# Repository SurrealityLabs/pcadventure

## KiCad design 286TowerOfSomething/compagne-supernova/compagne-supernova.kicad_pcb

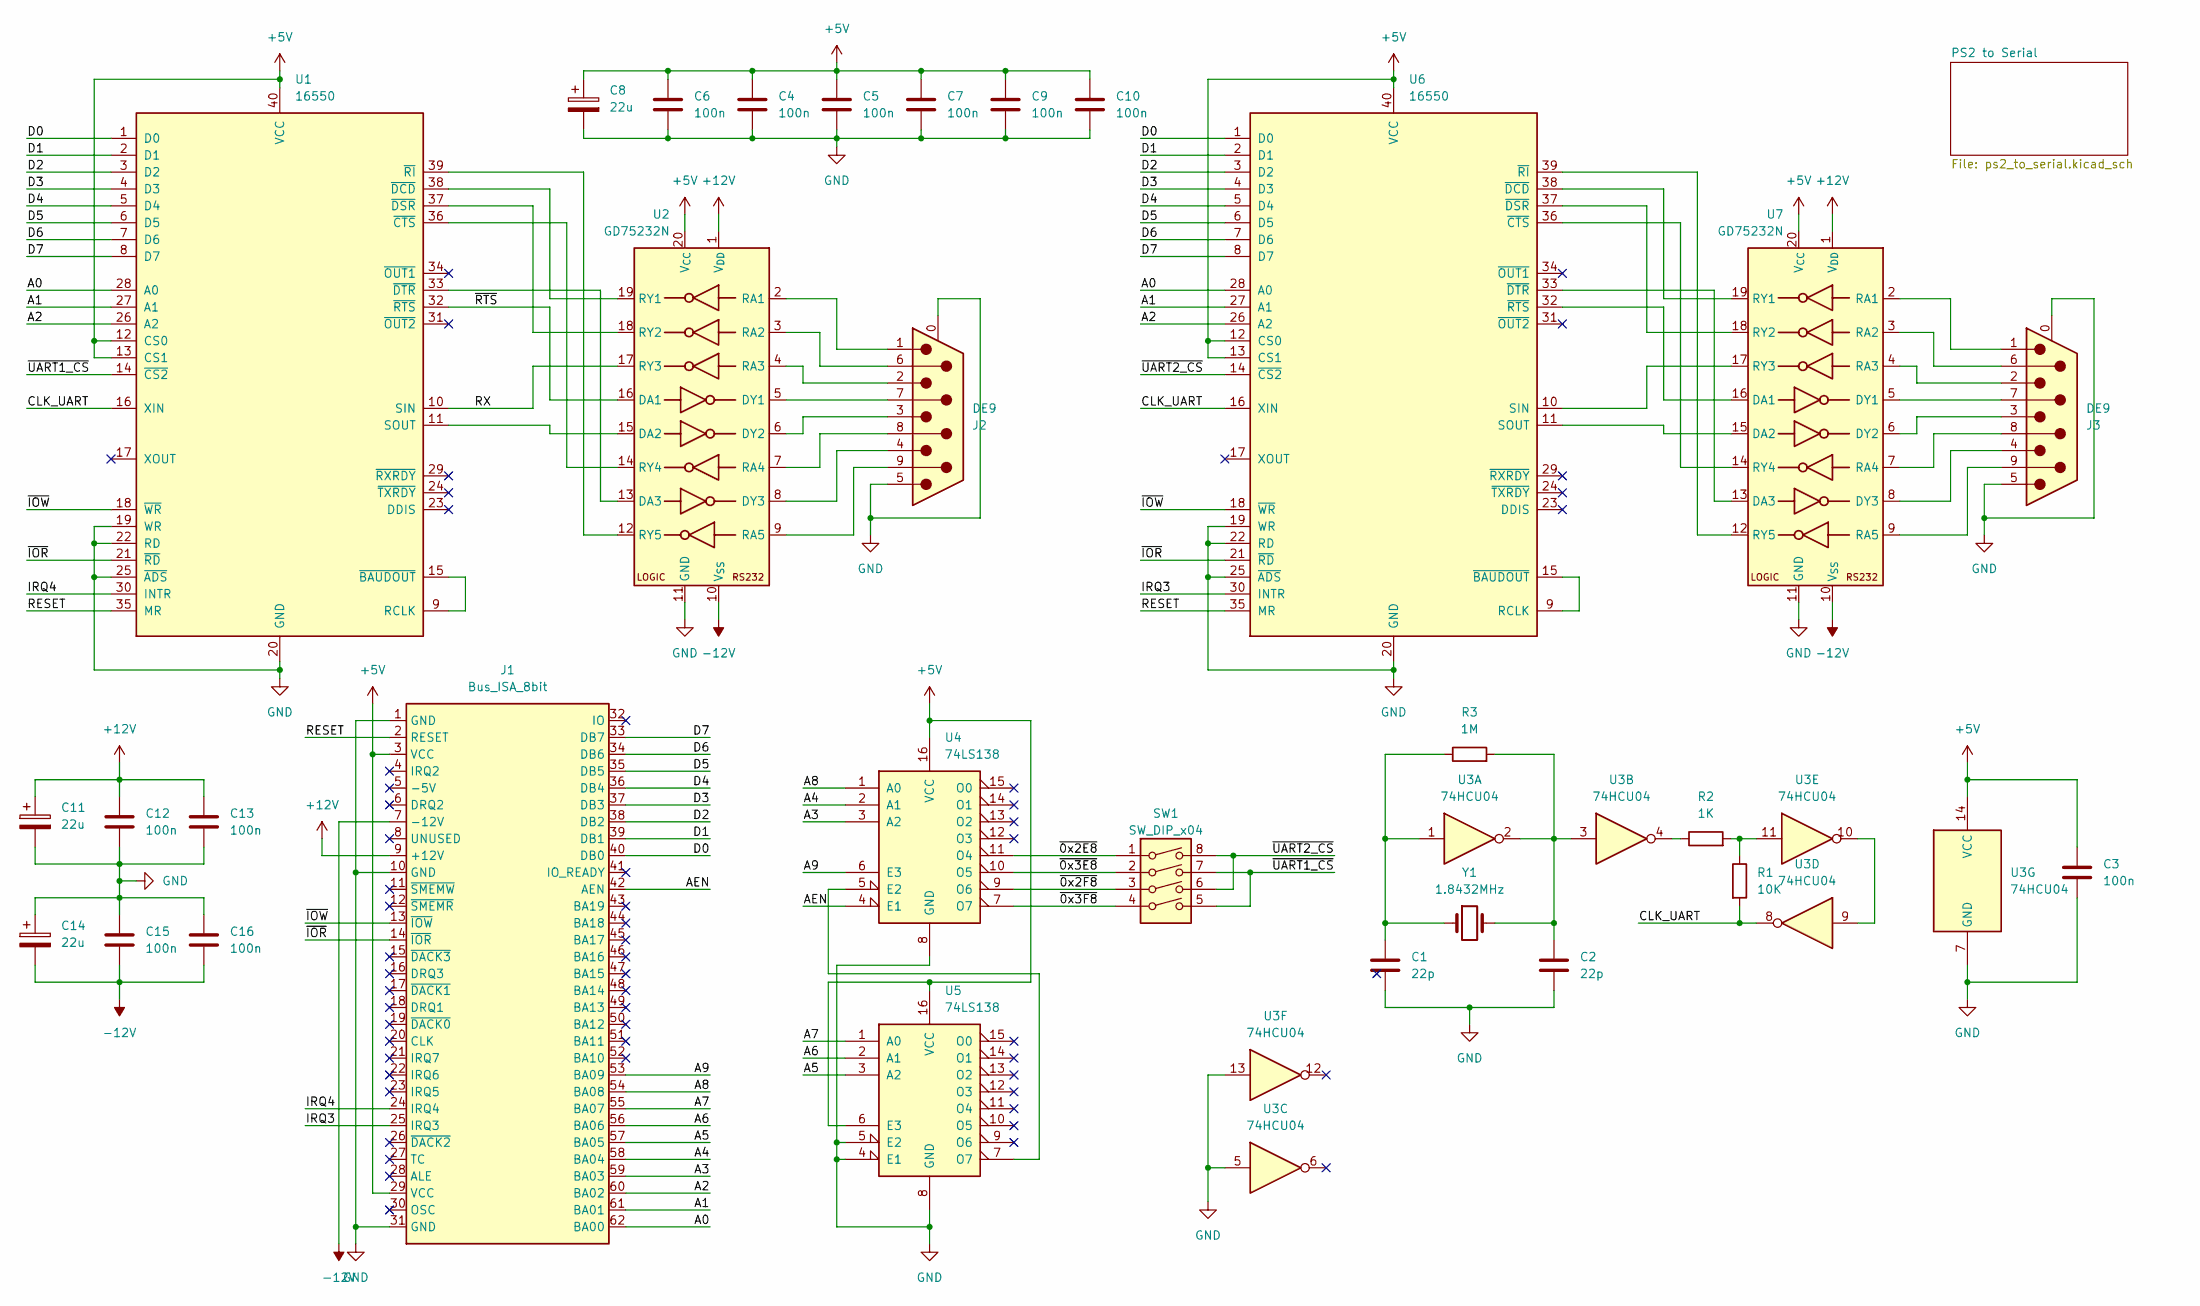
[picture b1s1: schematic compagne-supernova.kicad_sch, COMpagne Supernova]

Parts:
C1, C2: 22p; C_0603_1608Metric_Pad1.08x0.95mm_HandSolder
C3, C4, C5, C6, C7, C9, C10, C12, C13, C15, C16: 100n; C_0603_1608Metric_Pad1.08x0.95mm_HandSolder
C8, C11, C14: 22u; CP_Elec_5x5.3
J1: Bus_ISA_8bit; BUS_AT_8BIT
J2, J3: DE9; DSUB-9_Male_Horizontal_P2.77x2.84mm_EdgePinOffset7.70mm_Hou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
R1: 10K; R_0603_1608Metric_Pad0.98x0.95mm_HandSolder
R2: 1K; R_0603_1608Metric_Pad0.98x0.95mm_HandSolder
R3: 1M; R_0603_1608Metric_Pad0.98x0.95mm_HandSolder
SW1: SW_DIP_x04; SW_DIP_SPSTx04_Slide_9.78x12.34mm_W7.62mm_P2.54mm
U1, U6: 16550; DIP-40_W15.24mm
U2, U7: GD75232N; DIP-20_W7.62mm
U3: 74HCU04; SO-14_3.9x8.65mm_P1.27mm
U4, U5: 74LS138; DIP-16_W7.62mm
Y1: 1.8432MHz; Crystal_HC49-U_Vertical

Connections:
+5V: C3.1, C4.1, C5.1, C6.1, C7.1, C8.1, C9.1, C10.1, J1.3 (VCC), J1.29 (VCC), U1.12 (CS0), U1.13 (CS1), U1.40 (VCC), U2.20 (V_{CC}), U3.14 (VCC), U4.16 (VCC), U5.6 (E3), U5.16 (VCC), U6.12 (CS0), U6.13 (CS1), U6.40 (VCC), U7.20 (V_{CC}); also elsewhere on the board
+12V: C11.1, C12.1, C13.1, J1.9 (+12V), U2.1 (V_{DD}), U7.1 (V_{DD})
-12V: C14.2, C15.2, C16.2, J1.7 (-12V), U2.10 (V_{SS}), U7.10 (V_{SS})
/A0: J1.62 (BA00), U1.28 (A0), U6.28 (A0)
/A1: J1.61 (BA01), U1.27 (A1), U6.27 (A1)
/A2: J1.60 (BA02), U1.26 (A2), U6.26 (A2)
/A3: J1.59 (BA03), U4.3 (A2)
/A4: J1.58 (BA04), U4.2 (A1)
/A5: J1.57 (BA05), U5.3 (A2)
/A6: J1.56 (BA06), U5.2 (A1)
/A7: J1.55 (BA07), U5.1 (A0)
/A8: J1.54 (BA08), U4.1 (A0)
/A9: J1.53 (BA09), U4.6 (E3)
/AEN: J1.42 (AEN), U4.4 (E1)
/CLK_UART: R1.2, U1.16 (XIN), U3.8, U6.16 (XIN)
/D0: J1.40 (DB0), U1.1 (D0), U6.1 (D0)
/D1: J1.39 (DB1), U1.2 (D1), U6.2 (D1)
/D2: J1.38 (DB2), U1.3 (D2), U6.3 (D2)
/D3: J1.37 (DB3), U1.4 (D3), U6.4 (D3)
/D4: J1.36 (DB4), U1.5 (D4), U6.5 (D4)
/D5: J1.35 (DB5), U1.6 (D5), U6.6 (D5)
/D6: J1.34 (DB6), U1.7 (D6), U6.7 (D6)
/D7: J1.33 (DB7), U1.8 (D7), U6.8 (D7)
/IRQ3: J1.25 (IRQ3), U6.30 (INTR)
/IRQ4: J1.24 (IRQ4), U1.30 (INTR)
/RESET: J1.2 (RESET), U1.35 (MR), U6.35 (MR)
/RX: U1.10 (SIN), U2.17 (RY3)
/~0x2E8: SW1.1, U4.11 (O4)
/~0x2F8: SW1.3, U4.9 (O6)
/~0x3E8: SW1.2, U4.10 (O5)
/~0x3F8: SW1.4, U4.7 (O7)
/~IOR: J1.14 (~IOR), U1.21 (~RD), U6.21 (~RD)
/~IOW: J1.13 (~IOW), U1.18 (~WR), U6.18 (~WR)
/~RTS: U1.32 (~RTS), U2.16 (DA1)
/~UART1_CS: SW1.5, SW1.7, U1.14 (~CS2)
/~UART2_CS: SW1.6, SW1.8, U6.14 (~CS2)
GND: C1.2, C2.2, C3.2, C4.2, C5.2, C6.2, C7.2, C8.2, C9.2, C10.2, C11.2, C12.2, C13.2, C14.1, C15.1, C16.1, J1.1 (GND), J1.10 (GND), J1.31 (GND), J2.0 (PAD), J2.5, J3.0 (PAD), J3.5, U1.19 (WR), U1.20 (GND), U1.22 (RD), U1.25 (~ADS), U2.11 (GND), U3.5, U3.7 (GND), U3.13, U4.8 (GND), U5.4 (E1), U5.5 (E2), U5.8 (GND), U6.19 (WR), U6.20 (GND), U6.22 (RD), U6.25 (~ADS), U7.11 (GND); also elsewhere on the board
unnamed: C1.1, R3.1, U3.1, Y1.1
unnamed: C2.1, R3.2, U3.2, U3.3, Y1.2
unnamed: R1.1, R2.2, U3.11
unnamed: R2.1, U3.4
unnamed: U1.9 (RCLK), U1.15 (~BAUDOUT)
unnamed: U1.11 (SOUT), U2.15 (DA2)
unnamed: U1.36 (~CTS), U2.14 (RY4)
unnamed: U1.38 (~DCD), U2.19 (RY1)
unnamed: U1.37 (~DSR), U2.18 (RY2)
unnamed: U1.33 (~DTR), U2.13 (DA3)
unnamed: U1.39 (~RI), U2.12 (RY5)
unnamed: J2.7, U2.5 (DY1)
unnamed: J2.3, U2.6 (DY2)
unnamed: J2.4, U2.8 (DY3)
unnamed: J2.1, U2.2 (RA1)
unnamed: J2.6, U2.3 (RA2)
unnamed: J2.2, U2.4 (RA3)
unnamed: J2.8, U2.7 (RA4)
unnamed: J2.9, U2.9 (RA5)
unnamed: U3.9, U3.10
unnamed: U4.5 (E2), U5.7 (O7)
unnamed: U6.9 (RCLK), U6.15 (~BAUDOUT)
unnamed: U6.10 (SIN), U7.17 (RY3)
unnamed: U6.11 (SOUT), U7.15 (DA2)
unnamed: U6.36 (~CTS), U7.14 (RY4)
unnamed: U6.38 (~DCD), U7.19 (RY1)
unnamed: U6.37 (~DSR), U7.18 (RY2)
unnamed: U6.33 (~DTR), U7.13 (DA3)
unnamed: U6.39 (~RI), U7.12 (RY5)
unnamed: U6.32 (~RTS), U7.16 (DA1)
unnamed: J3.7, U7.5 (DY1)
unnamed: J3.3, U7.6 (DY2)
unnamed: J3.4, U7.8 (DY3)
unnamed: J3.1, U7.2 (RA1)
unnamed: J3.6, U7.3 (RA2)
unnamed: J3.2, U7.4 (RA3)
unnamed: J3.8, U7.7 (RA4)
unnamed: J3.9, U7.9 (RA5)

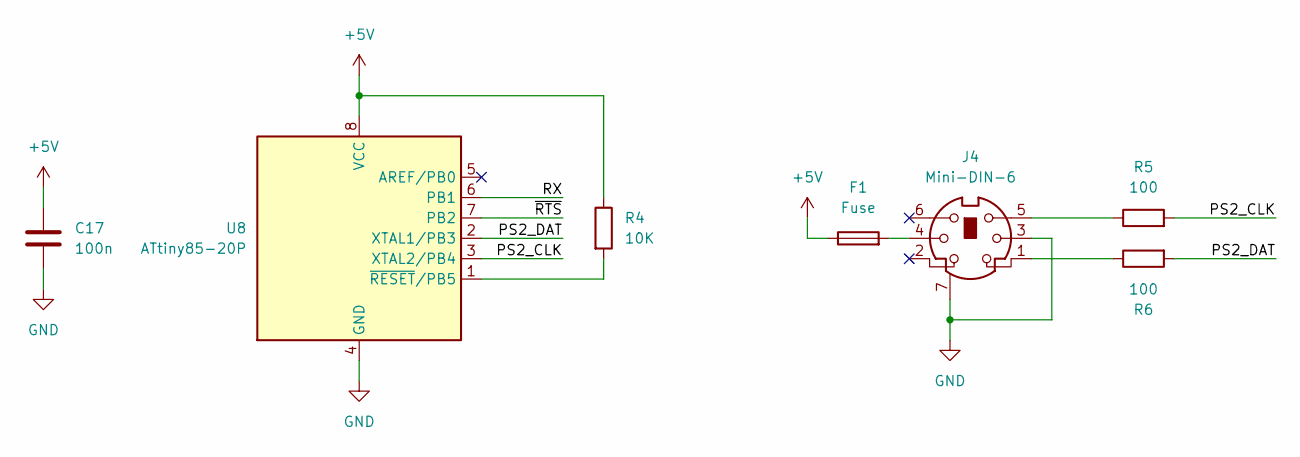
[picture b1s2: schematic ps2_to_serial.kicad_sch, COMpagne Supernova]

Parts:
C17: 100n; C_0603_1608Metric_Pad1.08x0.95mm_HandSolder
F1: Fuse; Fuse_1206_3216Metric_Pad1.42x1.75mm_HandSolder
J4: Mini-DIN-6; CUI_MD-60SGK
R4: 10K; R_0603_1608Metric_Pad0.98x0.95mm_HandSolder
R5, R6: 100; R_0603_1608Metric_Pad0.98x0.95mm_HandSolder
U8: ATtiny85-20P; DIP-8_W7.62mm

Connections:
+5V: C17.1, F1.1, R4.1, U8.8 (VCC); also elsewhere on the board
/PS2 to Serial/PS2_CLK: R5.2, U8.3 (XTAL2/PB4)
/PS2 to Serial/PS2_DAT: R6.2, U8.2 (XTAL1/PB3)
/PS2 to Serial/RX: U8.6 (PB1)
/PS2 to Serial/~RTS: U8.7 (PB2)
GND: C17.2, J4.3, J4.7, U8.4 (GND); also elsewhere on the board
unnamed: F1.2, J4.4
unnamed: J4.1, R6.1
unnamed: J4.5, R5.1
unnamed: R4.2, U8.1 (~RESET/PB5)

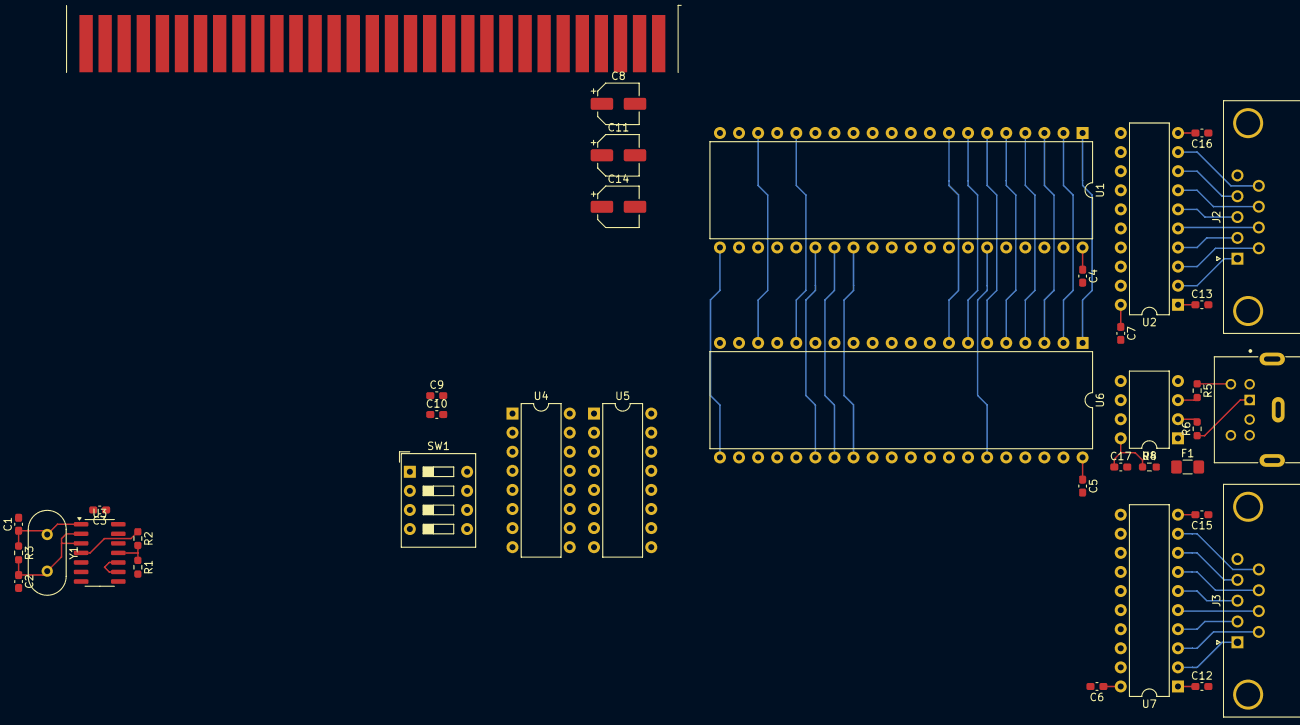
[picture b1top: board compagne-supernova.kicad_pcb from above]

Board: 2 copper layers, 38 parts (0 on the bottom side), 81 nets.

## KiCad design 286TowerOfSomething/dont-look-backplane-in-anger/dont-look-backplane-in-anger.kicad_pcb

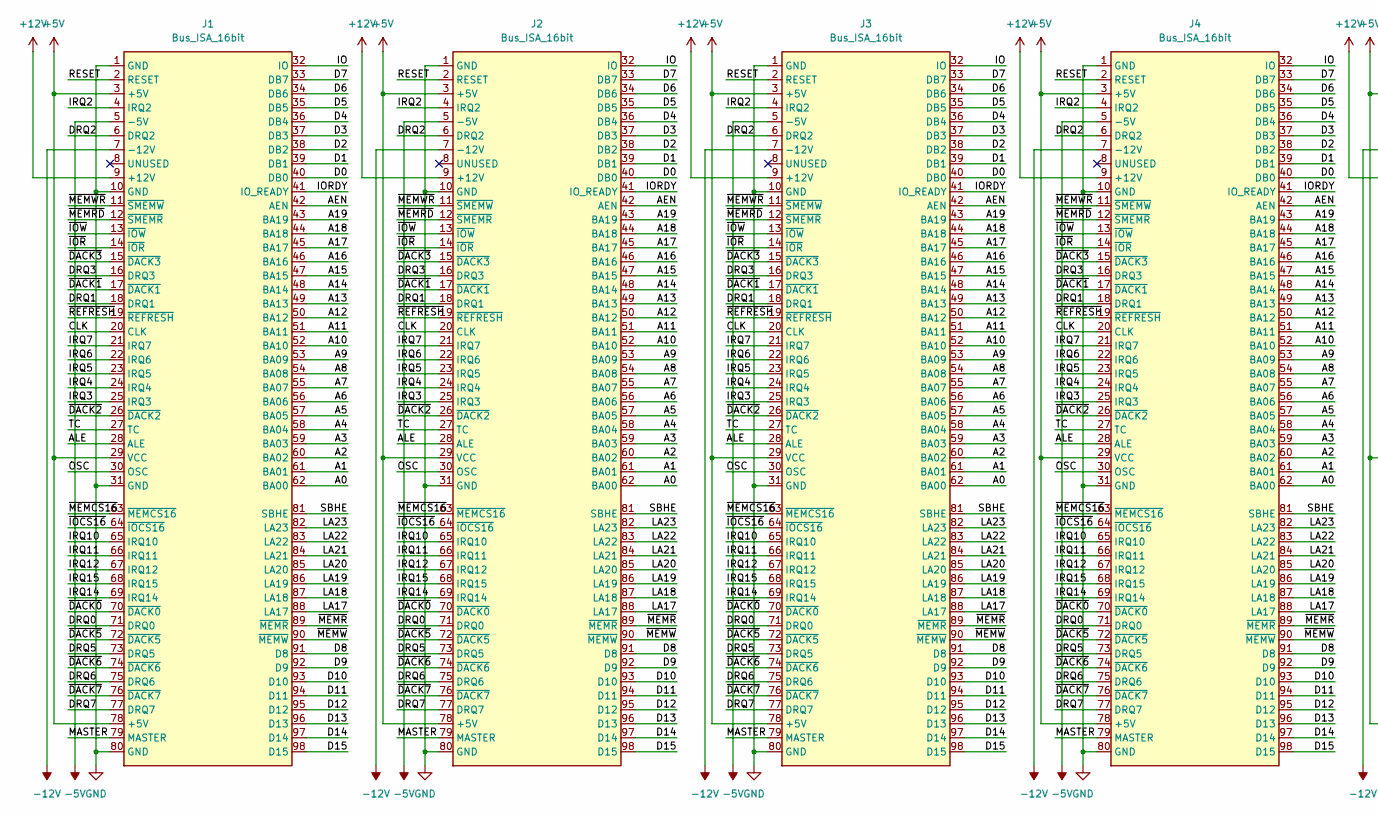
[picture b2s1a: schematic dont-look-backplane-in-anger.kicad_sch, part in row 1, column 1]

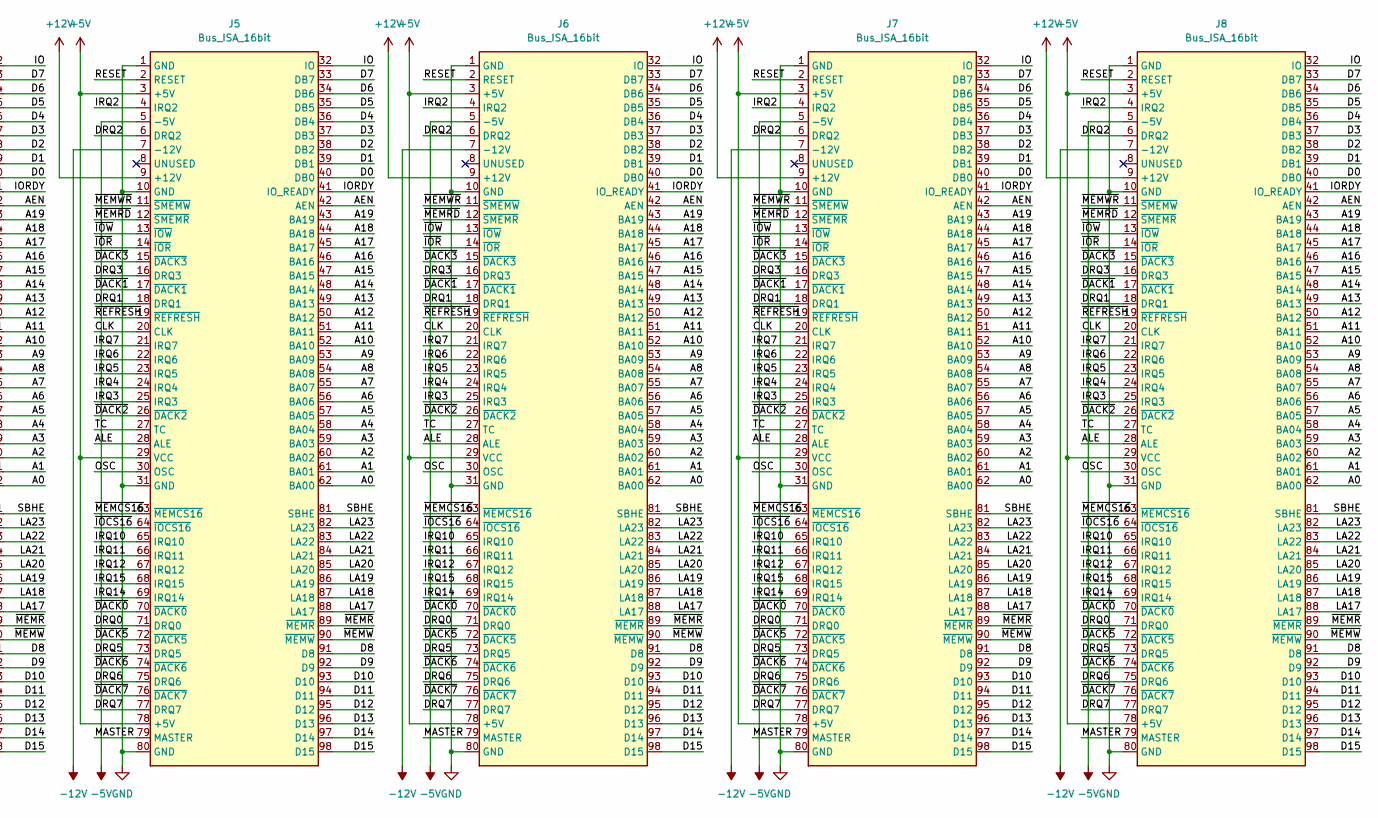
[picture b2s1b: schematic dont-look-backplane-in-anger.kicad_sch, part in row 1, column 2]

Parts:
J1, J2, J3, J4, J5, J6, J7, J8: Bus_ISA_16bit; 645169-3

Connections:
+5V: J1.3 (+5V), J1.29 (VCC), J1.78 (+5V), J2.3 (+5V), J2.29 (VCC), J2.78 (+5V), J3.3 (+5V), J3.29 (VCC), J3.78 (+5V), J4.3 (+5V), J4.29 (VCC), J4.78 (+5V), J5.3 (+5V), J5.29 (VCC), J5.78 (+5V), J6.3 (+5V), J6.29 (VCC), J6.78 (+5V), J7.3 (+5V), J7.29 (VCC), J7.78 (+5V), J8.3 (+5V), J8.29 (VCC), J8.78 (+5V)
+12V: J1.9 (+12V), J2.9 (+12V), J3.9 (+12V), J4.9 (+12V), J5.9 (+12V), J6.9 (+12V), J7.9 (+12V), J8.9 (+12V)
-5V: J1.5 (-5V), J2.5 (-5V), J3.5 (-5V), J4.5 (-5V), J5.5 (-5V), J6.5 (-5V), J7.5 (-5V), J8.5 (-5V)
-12V: J1.7 (-12V), J2.7 (-12V), J3.7 (-12V), J4.7 (-12V), J5.7 (-12V), J6.7 (-12V), J7.7 (-12V), J8.7 (-12V)
/A0: J1.62 (BA00), J2.62 (BA00), J3.62 (BA00), J4.62 (BA00), J5.62 (BA00), J6.62 (BA00), J7.62 (BA00), J8.62 (BA00)
/A1: J1.61 (BA01), J2.61 (BA01), J3.61 (BA01), J4.61 (BA01), J5.61 (BA01), J6.61 (BA01), J7.61 (BA01), J8.61 (BA01)
/A2: J1.60 (BA02), J2.60 (BA02), J3.60 (BA02), J4.60 (BA02), J5.60 (BA02), J6.60 (BA02), J7.60 (BA02), J8.60 (BA02)
/A3: J1.59 (BA03), J2.59 (BA03), J3.59 (BA03), J4.59 (BA03), J5.59 (BA03), J6.59 (BA03), J7.59 (BA03), J8.59 (BA03)
/A4: J1.58 (BA04), J2.58 (BA04), J3.58 (BA04), J4.58 (BA04), J5.58 (BA04), J6.58 (BA04), J7.58 (BA04), J8.58 (BA04)
/A5: J1.57 (BA05), J2.57 (BA05), J3.57 (BA05), J4.57 (BA05), J5.57 (BA05), J6.57 (BA05), J7.57 (BA05), J8.57 (BA05)
/A6: J1.56 (BA06), J2.56 (BA06), J3.56 (BA06), J4.56 (BA06), J5.56 (BA06), J6.56 (BA06), J7.56 (BA06), J8.56 (BA06)
/A7: J1.55 (BA07), J2.55 (BA07), J3.55 (BA07), J4.55 (BA07), J5.55 (BA07), J6.55 (BA07), J7.55 (BA07), J8.55 (BA07)
/A8: J1.54 (BA08), J2.54 (BA08), J3.54 (BA08), J4.54 (BA08), J5.54 (BA08), J6.54 (BA08), J7.54 (BA08), J8.54 (BA08)
/A9: J1.53 (BA09), J2.53 (BA09), J3.53 (BA09), J4.53 (BA09), J5.53 (BA09), J6.53 (BA09), J7.53 (BA09), J8.53 (BA09)
/A10: J1.52 (BA10), J2.52 (BA10), J3.52 (BA10), J4.52 (BA10), J5.52 (BA10), J6.52 (BA10), J7.52 (BA10), J8.52 (BA10)
/A11: J1.51 (BA11), J2.51 (BA11), J3.51 (BA11), J4.51 (BA11), J5.51 (BA11), J6.51 (BA11), J7.51 (BA11), J8.51 (BA11)
/A12: J1.50 (BA12), J2.50 (BA12), J3.50 (BA12), J4.50 (BA12), J5.50 (BA12), J6.50 (BA12), J7.50 (BA12), J8.50 (BA12)
/A13: J1.49 (BA13), J2.49 (BA13), J3.49 (BA13), J4.49 (BA13), J5.49 (BA13), J6.49 (BA13), J7.49 (BA13), J8.49 (BA13)
/A14: J1.48 (BA14), J2.48 (BA14), J3.48 (BA14), J4.48 (BA14), J5.48 (BA14), J6.48 (BA14), J7.48 (BA14), J8.48 (BA14)
/A15: J1.47 (BA15), J2.47 (BA15), J3.47 (BA15), J4.47 (BA15), J5.47 (BA15), J6.47 (BA15), J7.47 (BA15), J8.47 (BA15)
/A16: J1.46 (BA16), J2.46 (BA16), J3.46 (BA16), J4.46 (BA16), J5.46 (BA16), J6.46 (BA16), J7.46 (BA16), J8.46 (BA16)
/A17: J1.45 (BA17), J2.45 (BA17), J3.45 (BA17), J4.45 (BA17), J5.45 (BA17), J6.45 (BA17), J7.45 (BA17), J8.45 (BA17)
/A18: J1.44 (BA18), J2.44 (BA18), J3.44 (BA18), J4.44 (BA18), J5.44 (BA18), J6.44 (BA18), J7.44 (BA18), J8.44 (BA18)
/A19: J1.43 (BA19), J2.43 (BA19), J3.43 (BA19), J4.43 (BA19), J5.43 (BA19), J6.43 (BA19), J7.43 (BA19), J8.43 (BA19)
/AEN: J1.42 (AEN), J2.42 (AEN), J3.42 (AEN), J4.42 (AEN), J5.42 (AEN), J6.42 (AEN), J7.42 (AEN), J8.42 (AEN)
/ALE: J1.28 (ALE), J2.28 (ALE), J3.28 (ALE), J4.28 (ALE), J5.28 (ALE), J6.28 (ALE), J7.28 (ALE), J8.28 (ALE)
/CLK: J1.20 (CLK), J2.20 (CLK), J3.20 (CLK), J4.20 (CLK), J5.20 (CLK), J6.20 (CLK), J7.20 (CLK), J8.20 (CLK)
/D0: J1.40 (DB0), J2.40 (DB0), J3.40 (DB0), J4.40 (DB0), J5.40 (DB0), J6.40 (DB0), J7.40 (DB0), J8.40 (DB0)
/D1: J1.39 (DB1), J2.39 (DB1), J3.39 (DB1), J4.39 (DB1), J5.39 (DB1), J6.39 (DB1), J7.39 (DB1), J8.39 (DB1)
/D2: J1.38 (DB2), J2.38 (DB2), J3.38 (DB2), J4.38 (DB2), J5.38 (DB2), J6.38 (DB2), J7.38 (DB2), J8.38 (DB2)
/D3: J1.37 (DB3), J2.37 (DB3), J3.37 (DB3), J4.37 (DB3), J5.37 (DB3), J6.37 (DB3), J7.37 (DB3), J8.37 (DB3)
/D4: J1.36 (DB4), J2.36 (DB4), J3.36 (DB4), J4.36 (DB4), J5.36 (DB4), J6.36 (DB4), J7.36 (DB4), J8.36 (DB4)
/D5: J1.35 (DB5), J2.35 (DB5), J3.35 (DB5), J4.35 (DB5), J5.35 (DB5), J6.35 (DB5), J7.35 (DB5), J8.35 (DB5)
/D6: J1.34 (DB6), J2.34 (DB6), J3.34 (DB6), J4.34 (DB6), J5.34 (DB6), J6.34 (DB6), J7.34 (DB6), J8.34 (DB6)
/D7: J1.33 (DB7), J2.33 (DB7), J3.33 (DB7), J4.33 (DB7), J5.33 (DB7), J6.33 (DB7), J7.33 (DB7), J8.33 (DB7)
/D8: J1.91 (D8), J2.91 (D8), J3.91 (D8), J4.91 (D8), J5.91 (D8), J6.91 (D8), J7.91 (D8), J8.91 (D8)
/D9: J1.92 (D9), J2.92 (D9), J3.92 (D9), J4.92 (D9), J5.92 (D9), J6.92 (D9), J7.92 (D9), J8.92 (D9)
/D10: J1.93 (D10), J2.93 (D10), J3.93 (D10), J4.93 (D10), J5.93 (D10), J6.93 (D10), J7.93 (D10), J8.93 (D10)
/D11: J1.94 (D11), J2.94 (D11), J3.94 (D11), J4.94 (D11), J5.94 (D11), J6.94 (D11), J7.94 (D11), J8.94 (D11)
/D12: J1.95 (D12), J2.95 (D12), J3.95 (D12), J4.95 (D12), J5.95 (D12), J6.95 (D12), J7.95 (D12), J8.95 (D12)
/D13: J1.96 (D13), J2.96 (D13), J3.96 (D13), J4.96 (D13), J5.96 (D13), J6.96 (D13), J7.96 (D13), J8.96 (D13)
/D14: J1.97 (D14), J2.97 (D14), J3.97 (D14), J4.97 (D14), J5.97 (D14), J6.97 (D14), J7.97 (D14), J8.97 (D14)
/D15: J1.98 (D15), J2.98 (D15), J3.98 (D15), J4.98 (D15), J5.98 (D15), J6.98 (D15), J7.98 (D15), J8.98 (D15)
/DRQ0: J1.71 (DRQ0), J2.71 (DRQ0), J3.71 (DRQ0), J4.71 (DRQ0), J5.71 (DRQ0), J6.71 (DRQ0), J7.71 (DRQ0), J8.71 (DRQ0)
/DRQ1: J1.18 (DRQ1), J2.18 (DRQ1), J3.18 (DRQ1), J4.18 (DRQ1), J5.18 (DRQ1), J6.18 (DRQ1), J7.18 (DRQ1), J8.18 (DRQ1)
/DRQ2: J1.6 (DRQ2), J2.6 (DRQ2), J3.6 (DRQ2), J4.6 (DRQ2), J5.6 (DRQ2), J6.6 (DRQ2), J7.6 (DRQ2), J8.6 (DRQ2)
/DRQ3: J1.16 (DRQ3), J2.16 (DRQ3), J3.16 (DRQ3), J4.16 (DRQ3), J5.16 (DRQ3), J6.16 (DRQ3), J7.16 (DRQ3), J8.16 (DRQ3)
/DRQ5: J1.73 (DRQ5), J2.73 (DRQ5), J3.73 (DRQ5), J4.73 (DRQ5), J5.73 (DRQ5), J6.73 (DRQ5), J7.73 (DRQ5), J8.73 (DRQ5)
/DRQ6: J1.75 (DRQ6), J2.75 (DRQ6), J3.75 (DRQ6), J4.75 (DRQ6), J5.75 (DRQ6), J6.75 (DRQ6), J7.75 (DRQ6), J8.75 (DRQ6)
/DRQ7: J1.77 (DRQ7), J2.77 (DRQ7), J3.77 (DRQ7), J4.77 (DRQ7), J5.77 (DRQ7), J6.77 (DRQ7), J7.77 (DRQ7), J8.77 (DRQ7)
/IO: J1.32 (IO), J2.32 (IO), J3.32 (IO), J4.32 (IO), J5.32 (IO), J6.32 (IO), J7.32 (IO), J8.32 (IO)
/IORDY: J1.41 (IO_READY), J2.41 (IO_READY), J3.41 (IO_READY), J4.41 (IO_READY), J5.41 (IO_READY), J6.41 (IO_READY), J7.41 (IO_READY), J8.41 (IO_READY)
/IRQ2: J1.4 (IRQ2), J2.4 (IRQ2), J3.4 (IRQ2), J4.4 (IRQ2), J5.4 (IRQ2), J6.4 (IRQ2), J7.4 (IRQ2), J8.4 (IRQ2)
/IRQ3: J1.25 (IRQ3), J2.25 (IRQ3), J3.25 (IRQ3), J4.25 (IRQ3), J5.25 (IRQ3), J6.25 (IRQ3), J7.25 (IRQ3), J8.25 (IRQ3)
/IRQ4: J1.24 (IRQ4), J2.24 (IRQ4), J3.24 (IRQ4), J4.24 (IRQ4), J5.24 (IRQ4), J6.24 (IRQ4), J7.24 (IRQ4), J8.24 (IRQ4)
/IRQ5: J1.23 (IRQ5), J2.23 (IRQ5), J3.23 (IRQ5), J4.23 (IRQ5), J5.23 (IRQ5), J6.23 (IRQ5), J7.23 (IRQ5), J8.23 (IRQ5)
/IRQ6: J1.22 (IRQ6), J2.22 (IRQ6), J3.22 (IRQ6), J4.22 (IRQ6), J5.22 (IRQ6), J6.22 (IRQ6), J7.22 (IRQ6), J8.22 (IRQ6)
/IRQ7: J1.21 (IRQ7), J2.21 (IRQ7), J3.21 (IRQ7), J4.21 (IRQ7), J5.21 (IRQ7), J6.21 (IRQ7), J7.21 (IRQ7), J8.21 (IRQ7)
/IRQ10: J1.65 (IRQ10), J2.65 (IRQ10), J3.65 (IRQ10), J4.65 (IRQ10), J5.65 (IRQ10), J6.65 (IRQ10), J7.65 (IRQ10), J8.65 (IRQ10)
/IRQ11: J1.66 (IRQ11), J2.66 (IRQ11), J3.66 (IRQ11), J4.66 (IRQ11), J5.66 (IRQ11), J6.66 (IRQ11), J7.66 (IRQ11), J8.66 (IRQ11)
/IRQ12: J1.67 (IRQ12), J2.67 (IRQ12), J3.67 (IRQ12), J4.67 (IRQ12), J5.67 (IRQ12), J6.67 (IRQ12), J7.67 (IRQ12), J8.67 (IRQ12)
/IRQ14: J1.69 (IRQ14), J2.69 (IRQ14), J3.69 (IRQ14), J4.69 (IRQ14), J5.69 (IRQ14), J6.69 (IRQ14), J7.69 (IRQ14), J8.69 (IRQ14)
/IRQ15: J1.68 (IRQ15), J2.68 (IRQ15), J3.68 (IRQ15), J4.68 (IRQ15), J5.68 (IRQ15), J6.68 (IRQ15), J7.68 (IRQ15), J8.68 (IRQ15)
/LA17: J1.88 (LA17), J2.88 (LA17), J3.88 (LA17), J4.88 (LA17), J5.88 (LA17), J6.88 (LA17), J7.88 (LA17), J8.88 (LA17)
/LA18: J1.87 (LA18), J2.87 (LA18), J3.87 (LA18), J4.87 (LA18), J5.87 (LA18), J6.87 (LA18), J7.87 (LA18), J8.87 (LA18)
/LA19: J1.86 (LA19), J2.86 (LA19), J3.86 (LA19), J4.86 (LA19), J5.86 (LA19), J6.86 (LA19), J7.86 (LA19), J8.86 (LA19)
/LA20: J1.85 (LA20), J2.85 (LA20), J3.85 (LA20), J4.85 (LA20), J5.85 (LA20), J6.85 (LA20), J7.85 (LA20), J8.85 (LA20)
/LA21: J1.84 (LA21), J2.84 (LA21), J3.84 (LA21), J4.84 (LA21), J5.84 (LA21), J6.84 (LA21), J7.84 (LA21), J8.84 (LA21)
/LA22: J1.83 (LA22), J2.83 (LA22), J3.83 (LA22), J4.83 (LA22), J5.83 (LA22), J6.83 (LA22), J7.83 (LA22), J8.83 (LA22)
/LA23: J1.82 (LA23), J2.82 (LA23), J3.82 (LA23), J4.82 (LA23), J5.82 (LA23), J6.82 (LA23), J7.82 (LA23), J8.82 (LA23)
/MASTER: J1.79 (MASTER), J2.79 (MASTER), J3.79 (MASTER), J4.79 (MASTER), J5.79 (MASTER), J6.79 (MASTER), J7.79 (MASTER), J8.79 (MASTER)
/OSC: J1.30 (OSC), J2.30 (OSC), J3.30 (OSC), J4.30 (OSC), J5.30 (OSC), J6.30 (OSC), J7.30 (OSC), J8.30 (OSC)
/RESET: J1.2 (RESET), J2.2 (RESET), J3.2 (RESET), J4.2 (RESET), J5.2 (RESET), J6.2 (RESET), J7.2 (RESET), J8.2 (RESET)
/SBHE: J1.81 (SBHE), J2.81 (SBHE), J3.81 (SBHE), J4.81 (SBHE), J5.81 (SBHE), J6.81 (SBHE), J7.81 (SBHE), J8.81 (SBHE)
/TC: J1.27 (TC), J2.27 (TC), J3.27 (TC), J4.27 (TC), J5.27 (TC), J6.27 (TC), J7.27 (TC), J8.27 (TC)
/~DACK0: J1.70 (~DACK0), J2.70 (~DACK0), J3.70 (~DACK0), J4.70 (~DACK0), J5.70 (~DACK0), J6.70 (~DACK0), J7.70 (~DACK0), J8.70 (~DACK0)
/~DACK1: J1.17 (~DACK1), J2.17 (~DACK1), J3.17 (~DACK1), J4.17 (~DACK1), J5.17 (~DACK1), J6.17 (~DACK1), J7.17 (~DACK1), J8.17 (~DACK1)
/~DACK2: J1.26 (~DACK2), J2.26 (~DACK2), J3.26 (~DACK2), J4.26 (~DACK2), J5.26 (~DACK2), J6.26 (~DACK2), J7.26 (~DACK2), J8.26 (~DACK2)
/~DACK3: J1.15 (~DACK3), J2.15 (~DACK3), J3.15 (~DACK3), J4.15 (~DACK3), J5.15 (~DACK3), J6.15 (~DACK3), J7.15 (~DACK3), J8.15 (~DACK3)
/~DACK5: J1.72 (~DACK5), J2.72 (~DACK5), J3.72 (~DACK5), J4.72 (~DACK5), J5.72 (~DACK5), J6.72 (~DACK5), J7.72 (~DACK5), J8.72 (~DACK5)
/~DACK6: J1.74 (~DACK6), J2.74 (~DACK6), J3.74 (~DACK6), J4.74 (~DACK6), J5.74 (~DACK6), J6.74 (~DACK6), J7.74 (~DACK6), J8.74 (~DACK6)
/~DACK7: J1.76 (~DACK7), J2.76 (~DACK7), J3.76 (~DACK7), J4.76 (~DACK7), J5.76 (~DACK7), J6.76 (~DACK7), J7.76 (~DACK7), J8.76 (~DACK7)
/~IOCS16: J1.64 (~IOCS16), J2.64 (~IOCS16), J3.64 (~IOCS16), J4.64 (~IOCS16), J5.64 (~IOCS16), J6.64 (~IOCS16), J7.64 (~IOCS16), J8.64 (~IOCS16)
/~IOR: J1.14 (~IOR), J2.14 (~IOR), J3.14 (~IOR), J4.14 (~IOR), J5.14 (~IOR), J6.14 (~IOR), J7.14 (~IOR), J8.14 (~IOR)
/~IOW: J1.13 (~IOW), J2.13 (~IOW), J3.13 (~IOW), J4.13 (~IOW), J5.13 (~IOW), J6.13 (~IOW), J7.13 (~IOW), J8.13 (~IOW)
/~MEMCS16: J1.63 (~MEMCS16), J2.63 (~MEMCS16), J3.63 (~MEMCS16), J4.63 (~MEMCS16), J5.63 (~MEMCS16), J6.63 (~MEMCS16), J7.63 (~MEMCS16), J8.63 (~MEMCS16)
/~MEMRD: J1.12 (~SMEMR), J2.12 (~SMEMR), J3.12 (~SMEMR), J4.12 (~SMEMR), J5.12 (~SMEMR), J6.12 (~SMEMR), J7.12 (~SMEMR), J8.12 (~SMEMR)
/~MEMR: J1.89 (~MEMR), J2.89 (~MEMR), J3.89 (~MEMR), J4.89 (~MEMR), J5.89 (~MEMR), J6.89 (~MEMR), J7.89 (~MEMR), J8.89 (~MEMR)
/~MEMWR: J1.11 (~SMEMW), J2.11 (~SMEMW), J3.11 (~SMEMW), J4.11 (~SMEMW), J5.11 (~SMEMW), J6.11 (~SMEMW), J7.11 (~SMEMW), J8.11 (~SMEMW)
/~MEMW: J1.90 (~MEMW), J2.90 (~MEMW), J3.90 (~MEMW), J4.90 (~MEMW), J5.90 (~MEMW), J6.90 (~MEMW), J7.90 (~MEMW), J8.90 (~MEMW)
/~REFRESH: J1.19 (~REFRESH), J2.19 (~REFRESH), J3.19 (~REFRESH), J4.19 (~REFRESH), J5.19 (~REFRESH), J6.19 (~REFRESH), J7.19 (~REFRESH), J8.19 (~REFRESH)
GND: J1.1 (GND), J1.10 (GND), J1.31 (GND), J1.80 (GND), J2.1 (GND), J2.10 (GND), J2.31 (GND), J2.80 (GND), J3.1 (GND), J3.10 (GND), J3.31 (GND), J3.80 (GND), J4.1 (GND), J4.10 (GND), J4.31 (GND), J4.80 (GND), J5.1 (GND), J5.10 (GND), J5.31 (GND), J5.80 (GND), J6.1 (GND), J6.10 (GND), J6.31 (GND), J6.80 (GND), J7.1 (GND), J7.10 (GND), J7.31 (GND), J7.80 (GND), J8.1 (GND), J8.10 (GND), J8.31 (GND), J8.80 (GND)

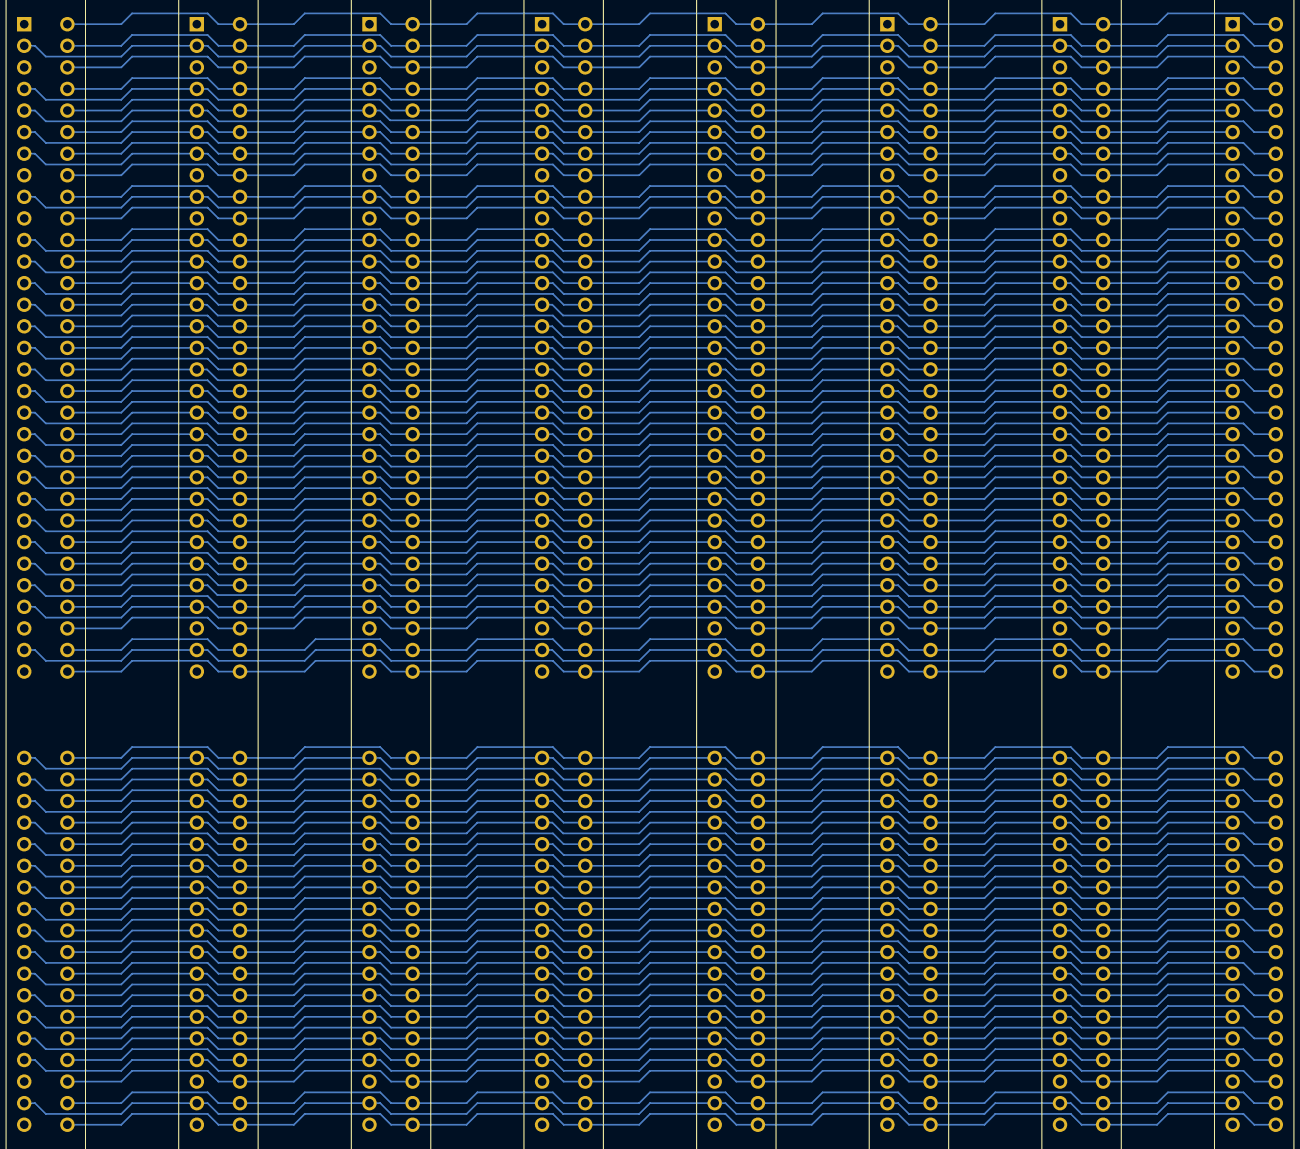
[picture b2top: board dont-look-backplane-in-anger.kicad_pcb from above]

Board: 2 copper layers, 8 parts (0 on the bottom side), 92 nets.
